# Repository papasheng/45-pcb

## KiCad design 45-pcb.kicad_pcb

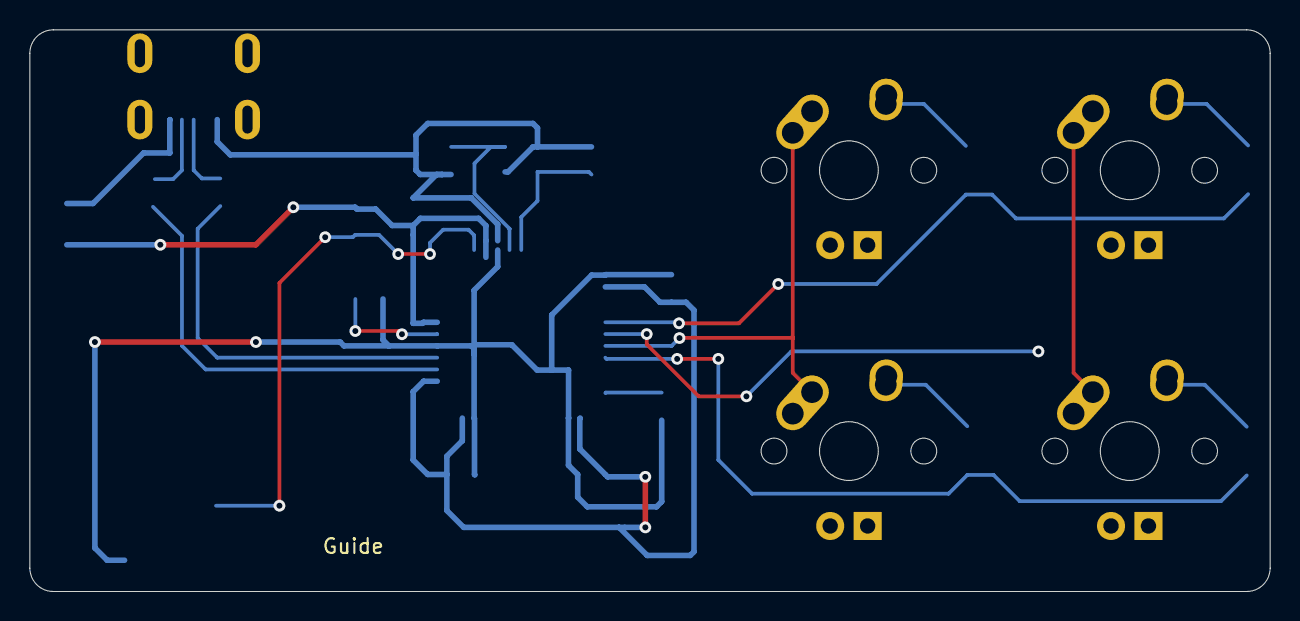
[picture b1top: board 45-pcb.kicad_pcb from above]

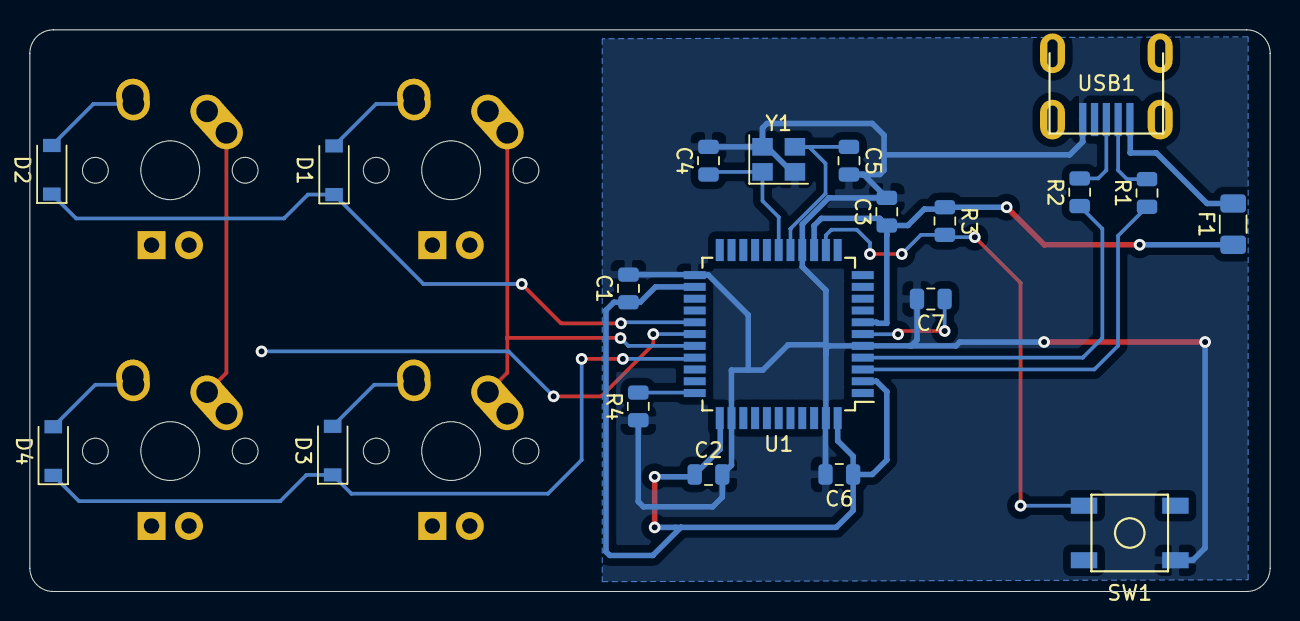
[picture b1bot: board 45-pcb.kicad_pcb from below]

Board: 2 copper layers, 84.1 x 38.1 mm, 24 parts (20 on the bottom side), 20 nets.

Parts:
C1, C2, C3: 0.1uF; C_0805_2012Metric
C4, C5: 22pF; C_0805_2012Metric
C6: 10uF; C_0805_2012Metric
C7: 1uF; C_0805_2012Metric
D1, D2, D3, D4: D_Small; D_SOD-123
F1: 500mA; Fuse_1206_3216Metric
MX1, MX2, MX3, MX4: MX-NoLED; MX-1U
R1, R2: 22; R_0805_2012Metric
R3, R4: 10k; R_0805_2012Metric
SW1: SW_Push; SKQG-1155865
U1: ATmega32U4-AU; TQFP-44_10x10mm_P0.8mm
USB1: Molex-0548190589
Y1: 16MHz; Crystal_SMD_3225-4Pin_3.2x2.5mm

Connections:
+5V: C1.1, C2.1, C3.1, C6.1, F1.1, R3.1, U1.2, U1.7, U1.14, U1.24, U1.34, U1.44
COL0: MX1.1, MX3.1, U1.29
COL1: MX2.1, MX4.1, U1.28
D+: R2.2, USB1.3
D-: R1.2, USB1.4
GND: C1.2, C2.2, C3.2, C4.2, C5.2, C6.2, C7.2, R4.1, SW1.1, U1.5, U1.15, U1.23, U1.35, U1.43, USB1.1, Y1.2, Y1.4
unnamed: C4.1, U1.17, Y1.1
unnamed: C5.1, U1.16, Y1.3
unnamed: C7.1, U1.6
unnamed: D1.2, MX1.2
unnamed: D2.2, MX2.2
unnamed: D3.2, MX3.2
unnamed: D4.2, MX4.2
unnamed: R1.1, U1.3
unnamed: R2.1, U1.4
unnamed: R3.2, SW1.2, U1.13
unnamed: R4.2, U1.33
ROW0: D1.1, D2.1, U1.27
ROW1: D3.1, D4.1, U1.30
VCC: F1.2, USB1.5

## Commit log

2020-06-23 KiCad Start
    First Initialisation of KiCad
2020-06-23 Add submodules
2020-06-23 Add footprint & symbol libs
2020-06-23 Schematics done
2020-06-23 Components Placed
    Routing Start
2020-06-23 Traces Finished
    PCB done
2020-06-23 Done
